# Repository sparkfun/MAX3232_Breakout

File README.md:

SparkFun Transceiver Breakout - MAX3232
===============================

[*SparkFun Transceiver Breakout - MAX3232 (BOB-11189)*](https://www.sparkfun.com/products/11189)

This is the RS232 converter IC that is capable of running at 3V and communicating with 5V logic.
We’ve taken the SOIC package MAX3232 and broken out all the pins you need to set up your RS232 to TTL connection. 
We’ve also included the necessary 0.1uF charge pump capacitors. 

Repository Contents
-------------------
* **/Hardware** - Eagle design files (.brd, .sch)
* **/Production** - Production panel files (.brd)

Documentation
-------------------
* **[Serial Communication](https://learn.sparkfun.com/tutorials/serial-communication)** - Basic tutorial on serial communication implemented on logic-level (TTL) and RS-232.
* **[Example Hookup Diagram](https://github.com/SparkfunTechSupport/Hookup-diagrams/blob/master/BOB-11189/BOB-11189%20hookup.jpg)**
* **[Fritzing Part](https://github.com/sparkfun/Fritzing_Parts/blob/main/products/11189-sfe_transceiver_breakout_max3232_rs232_converter_ttl.fzpz)**

License Information
-------------------

This product is _**open source**_! 

Please review the LICENSE.md file for license information. 

If you have any questions or concerns on licensing, please contact techsupport@sparkfun.com.

Distributed as-is; no warranty is given.

- Your friends at SparkFun.

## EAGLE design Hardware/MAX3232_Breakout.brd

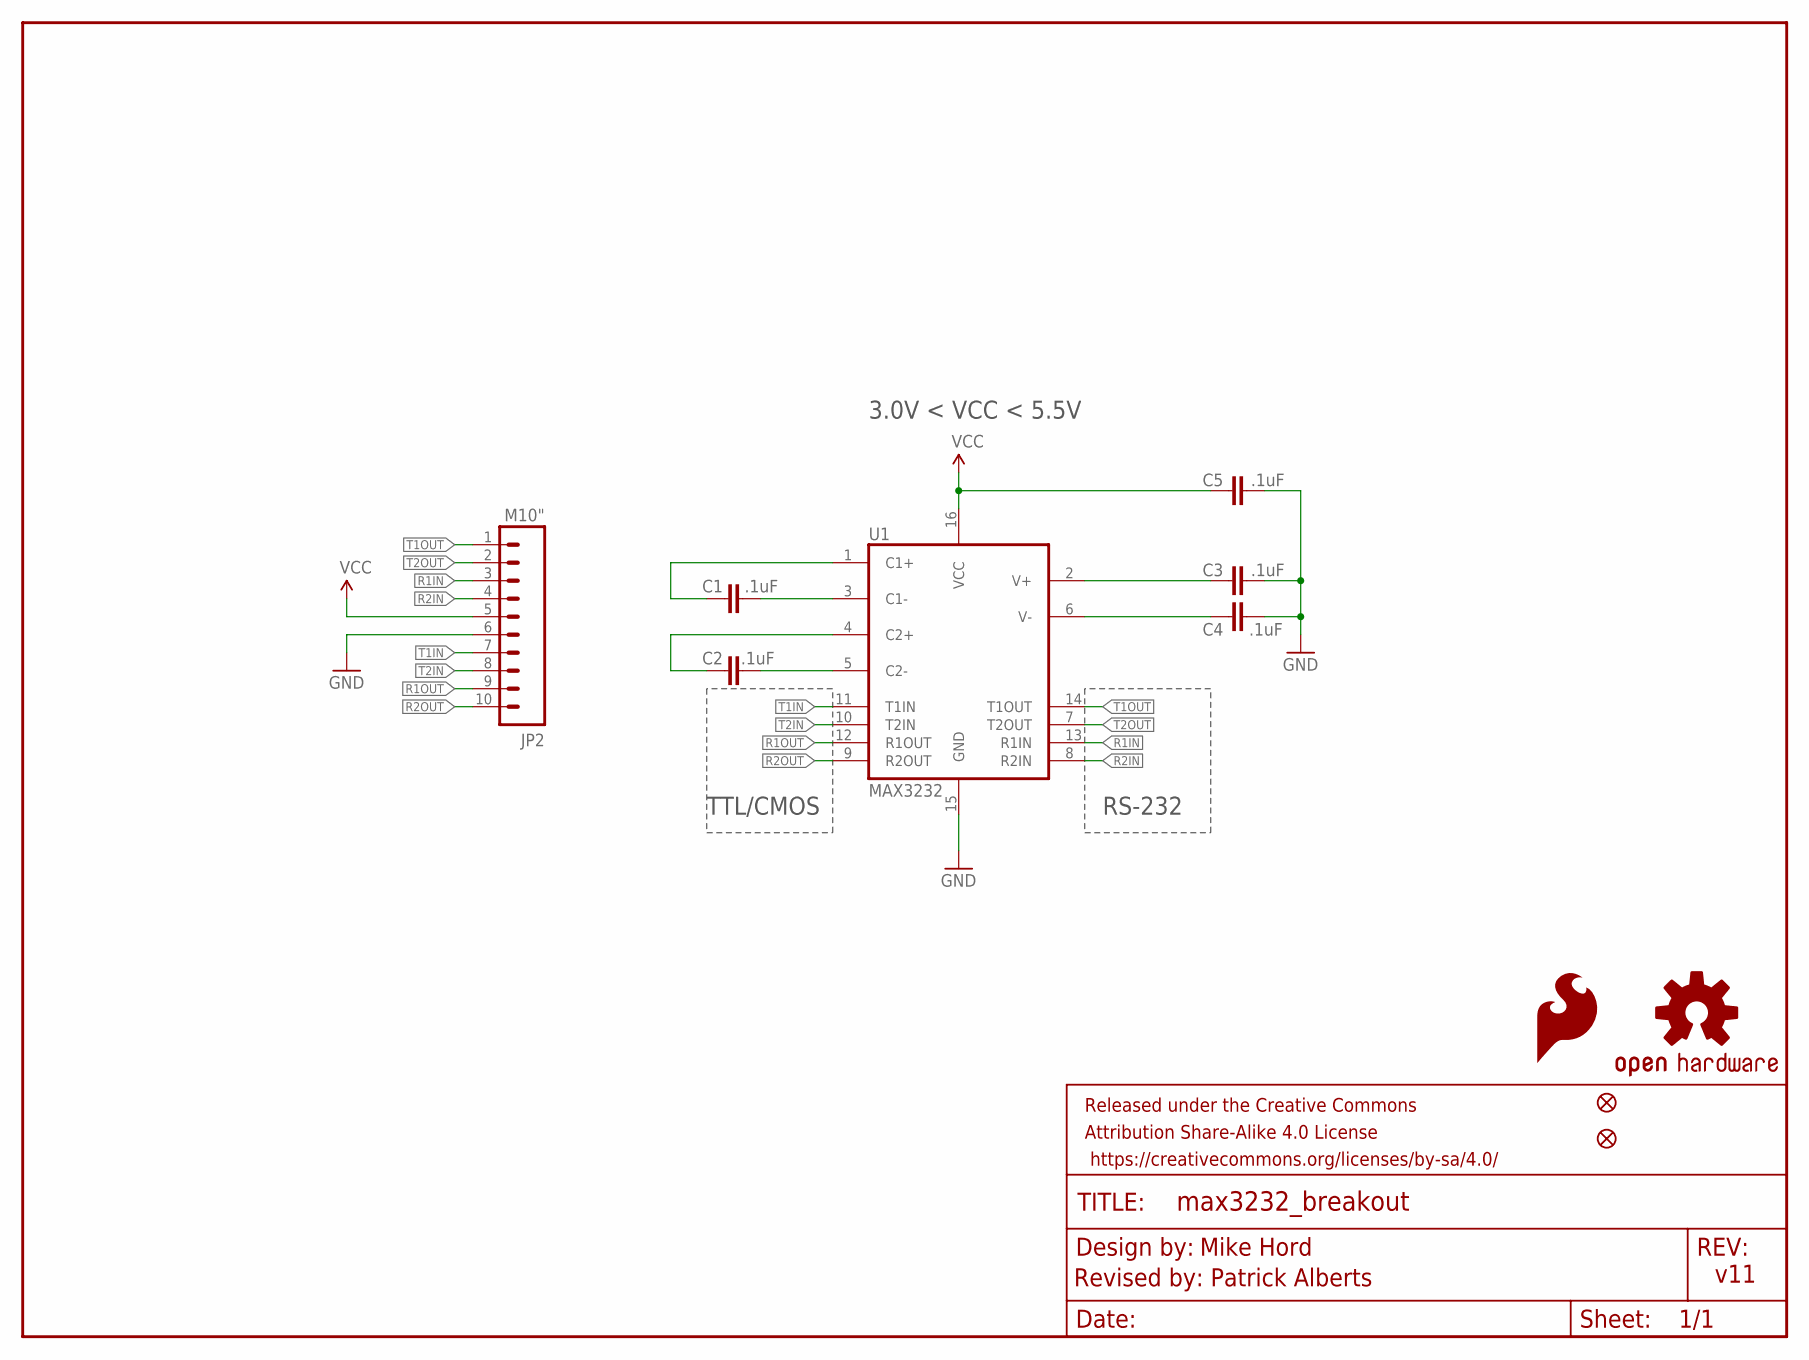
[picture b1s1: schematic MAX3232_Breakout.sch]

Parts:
C1, C2, C3, C4, C5: .1uF; 0603-CAP
FRAME1: FRAME-LETTER; CREATIVE_COMMONS
JP2: M10"; 1X10
JP3, JP4: FIDUCIALUFIDUCIAL; MICRO-FIDUCIAL
LOGO1: SFE_LOGO_FLAME.1_INCH; SFE_LOGO_FLAME_.1
U1: MAX3232; SO016
U$1: OSHW-LOGOS; OSHW-LOGO-S

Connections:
C1+: C1.1, U1.1 (C1+)
C1-: C1.2, U1.3 (C1-)
C2+: C2.1, U1.4 (C2+)
C2-: C2.2, U1.5 (C2-)
GND: C3.2, C4.2, C5.2, JP2.6, U1.15 (GND)
R1IN: JP2.3, U1.13 (R1IN)
R1OUT: JP2.9, U1.12 (R1OUT)
R2IN: JP2.4, U1.8 (R2IN)
R2OUT: JP2.10, U1.9 (R2OUT)
T1IN: JP2.7, U1.11 (T1IN)
T1OUT: JP2.1, U1.14 (T1OUT)
T2IN: JP2.8, U1.10 (T2IN)
T2OUT: JP2.2, U1.7 (T2OUT)
V+: C3.1, U1.2 (V+)
V-: C4.1, U1.6 (V-)
VCC: C5.1, JP2.5, U1.16 (VCC)

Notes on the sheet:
RS-232
TTL/CMOS
3.0V < VCC < 5.5V
Mike Hord
Revised by: Patrick Alberts
v11

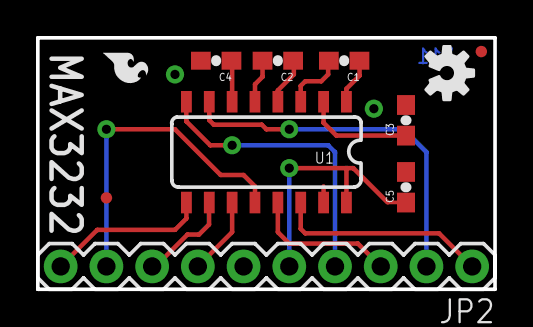
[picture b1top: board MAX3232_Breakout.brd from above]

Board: 2 copper layers, 25.4 x 14.0 mm, 12 parts (0 on the bottom side), 16 nets.

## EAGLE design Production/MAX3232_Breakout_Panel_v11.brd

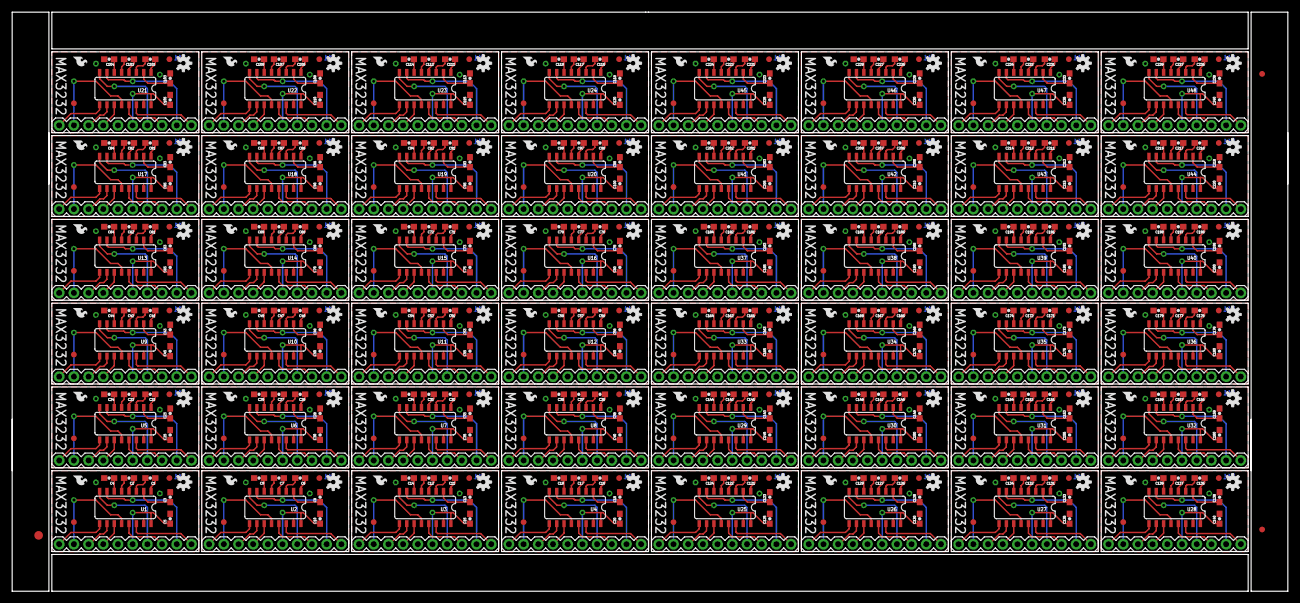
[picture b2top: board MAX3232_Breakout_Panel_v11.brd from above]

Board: 2 copper layers, 220.5 x 100.1 mm, 531 parts (0 on the bottom side), 768 nets.

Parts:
C1, C2, C3, C4, C5, C6, C7, C8, C9, C10, C11, C12, C13, C14, C15, C16, C17, C18, C19, C20, C21, C22, C23, C24, C25, C26, C27, C28, C29, C30, C31, C32, C33, C34, C35, C36, C37, C38, C39, C40, C41, C42, C43, C44, C45, C46, C47, C48, C49, C50, C51, C52, C53, C54, C55, C56, C57, C58, C59, C60, C61, C62, C63, C64, C65, C66, C67, C68, C69, C70, C71, C72, C73, C74, C75, C76, C77, C78, C79, C80, C81, C82, C83, C84, C85, C86, C87, C88, C89, C90, C91, C92, C93, C94, C95, C96, C97, C98, C99, C100, C101, C102, C103, C104, C105, C106, C107, C108, C109, C110, C111, C112, C113, C114, C115, C116, C117, C118, C119, C120, C121, C122, C123, C124, C125, C126, C127, C128, C129, C130, C131, C132, C133, C134, C135, C136, C137, C138, C139, C140, C141, C142, C143, C144, C145, C146, C147, C148, C149, C150, C151, C152, C153, C154, C155, C156, C157, C158, C159, C160, C161, C162, C163, C164, C165, C166, C167, C168, C169, C170, C171, C172, C173, C174, C175, C176, C177, C178, C179, C180, C181, C182, C183, C184, C185, C186, C187, C188, C189, C190, C191, C192, C193, C194, C195, C196, C197, C198, C199, C200, C201, C202, C203, C204, C205, C206, C207, C208, C209, C210, C211, C212, C213, C214, C215, C216, C217, C218, C219, C220, C221, C222, C223, C224, C225, C226, C227, C228, C229, C230, C231, C232, C233, C234, C235, C236, C237, C238, C239, C240: .1uF; 0603-CAP
E$1: FIDUCIAL-1.5X3
E$4, E$5: FIDUCIAL-1X2
FID1, FID2, FID3, FID4, FID5, FID6, FID7, FID8, FID9, FID10, FID11, FID12, FID13, FID14, FID15, FID16, FID17, FID18, FID19, FID20, FID21, FID22, FID23, FID24, FID25, FID26, FID27, FID28, FID29, FID30, FID31, FID32, FID33, FID34, FID35, FID36, FID37, FID38, FID39, FID40, FID41, FID42, FID43, FID44, FID45, FID46, FID47, FID48, FID49, FID50, FID51, FID52, FID53, FID54, FID55, FID56, FID57, FID58, FID59, FID60, FID61, FID62, FID63, FID64, FID65, FID66, FID67, FID68, FID69, FID70, FID71, FID72, FID73, FID74, FID75, FID76, FID77, FID78, FID79, FID80, FID81, FID82, FID83, FID84, FID85, FID86, FID87, FID88, FID89, FID90, FID91, FID92, FID93, FID94, FID95, FID96: FIDUCIAL1X2; FIDUCIAL-1X2
JP1, JP2, JP3, JP4, JP5, JP6, JP7, JP8, JP9, JP10, JP11, JP12, JP13, JP14, JP15, JP16, JP17, JP18, JP19, JP20, JP21, JP22, JP23, JP24, JP25, JP26, JP27, JP28, JP29, JP30, JP31, JP32, JP33, JP34, JP35, JP36, JP37, JP38, JP39, JP40, JP41, JP42, JP43, JP44, JP45, JP46, JP47, JP48: M10"; 1X10
LOGO1, LOGO2, LOGO3, LOGO4, LOGO5, LOGO6, LOGO7, LOGO8, LOGO9, LOGO10, LOGO11, LOGO12, LOGO13, LOGO14, LOGO15, LOGO16, LOGO17, LOGO18, LOGO19, LOGO20, LOGO21, LOGO22, LOGO23, LOGO24, LOGO25, LOGO26, LOGO27, LOGO28, LOGO29, LOGO30, LOGO31, LOGO32, LOGO33, LOGO34, LOGO35, LOGO36, LOGO37, LOGO38, LOGO39, LOGO40, LOGO41, LOGO42, LOGO43, LOGO44, LOGO45, LOGO46, LOGO47, LOGO48: SFE_LOGO_FLAME.1_INCH; SFE_LOGO_FLAME_.1
U1, U2, U3, U4, U5, U6, U7, U8, U9, U10, U11, U12, U13, U14, U15, U16, U17, U18, U19, U20, U21, U22, U23, U24, U25, U26, U27, U28, U29, U30, U31, U32, U33, U34, U35, U36, U37, U38, U39, U40, U41, U42, U43, U44, U45, U46, U47, U48: MAX3232; SO016
U$1, U$2, U$3, U$4, U$5, U$6, U$7, U$8, U$9, U$10, U$11, U$12, U$13, U$14, U$15, U$16, U$17, U$18, U$19, U$20, U$21, U$22, U$23, U$24, U$25, U$26, U$27, U$28, U$29, U$30, U$31, U$32, U$33, U$34, U$35, U$36, U$37, U$38, U$39, U$40, U$41, U$42, U$43, U$44, U$45, U$46, U$47, U$48: OSHW-LOGOS; OSHW-LOGO-S

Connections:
C1+: C1.1, U1.1
C1+1: C6.1, U2.1
C1+2: C11.1, U3.1
C1+3: C16.1, U4.1
C1+4: C21.1, U5.1
C1+5: C26.1, U6.1
C1+6: C31.1, U7.1
C1+7: C36.1, U8.1
C1+8: C41.1, U9.1
C1+9: C46.1, U10.1
C1+10: C51.1, U11.1
C1+11: C56.1, U12.1
C1+12: C61.1, U13.1
C1+13: C66.1, U14.1
C1+14: C71.1, U15.1
C1+15: C76.1, U16.1
C1+16: C81.1, U17.1
C1+17: C86.1, U18.1
C1+18: C91.1, U19.1
C1+19: C96.1, U20.1
C1+20: C101.1, U21.1
C1+21: C106.1, U22.1
C1+22: C111.1, U23.1
C1+23: C116.1, U24.1
C1+24: C121.1, U25.1
C1+25: C126.1, U26.1
C1+26: C131.1, U27.1
C1+27: C136.1, U28.1
C1+28: C141.1, U29.1
C1+29: C146.1, U30.1
C1+30: C151.1, U31.1
C1+31: C156.1, U32.1
C1+32: C161.1, U33.1
C1+33: C166.1, U34.1
C1+34: C171.1, U35.1
C1+35: C176.1, U36.1
C1+36: C181.1, U37.1
C1+37: C186.1, U38.1
C1+38: C191.1, U39.1
C1+39: C196.1, U40.1
C1+40: C201.1, U41.1
C1+41: C206.1, U42.1
C1+42: C211.1, U43.1
C1+43: C216.1, U44.1
C1+44: C221.1, U45.1
C1+45: C226.1, U46.1
C1+46: C231.1, U47.1
C1+47: C236.1, U48.1
C1-: C1.2, U1.3
C1-1: C6.2, U2.3
C1-2: C11.2, U3.3
C1-3: C16.2, U4.3
C1-4: C21.2, U5.3
C1-5: C26.2, U6.3
C1-6: C31.2, U7.3
C1-7: C36.2, U8.3
C1-8: C41.2, U9.3
C1-9: C46.2, U10.3
C1-10: C51.2, U11.3
C1-11: C56.2, U12.3
C1-12: C61.2, U13.3
C1-13: C66.2, U14.3
C1-14: C71.2, U15.3
C1-15: C76.2, U16.3
C1-16: C81.2, U17.3
C1-17: C86.2, U18.3
C1-18: C91.2, U19.3
C1-19: C96.2, U20.3
C1-20: C101.2, U21.3
C1-21: C106.2, U22.3
C1-22: C111.2, U23.3
C1-23: C116.2, U24.3
C1-24: C121.2, U25.3
C1-25: C126.2, U26.3
C1-26: C131.2, U27.3
C1-27: C136.2, U28.3
C1-28: C141.2, U29.3
C1-29: C146.2, U30.3
C1-30: C151.2, U31.3
C1-31: C156.2, U32.3
C1-32: C161.2, U33.3
C1-33: C166.2, U34.3
C1-34: C171.2, U35.3
C1-35: C176.2, U36.3
C1-36: C181.2, U37.3
C1-37: C186.2, U38.3
C1-38: C191.2, U39.3
C1-39: C196.2, U40.3
C1-40: C201.2, U41.3
C1-41: C206.2, U42.3
C1-42: C211.2, U43.3
C1-43: C216.2, U44.3
C1-44: C221.2, U45.3
C1-45: C226.2, U46.3
C1-46: C231.2, U47.3
C1-47: C236.2, U48.3
C2+: C2.1, U1.4
C2+1: C7.1, U2.4
C2+2: C12.1, U3.4
C2+3: C17.1, U4.4
C2+4: C22.1, U5.4
C2+5: C27.1, U6.4
C2+6: C32.1, U7.4
C2+7: C37.1, U8.4
C2+8: C42.1, U9.4
C2+9: C47.1, U10.4
C2+10: C52.1, U11.4
C2+11: C57.1, U12.4
C2+12: C62.1, U13.4
C2+13: C67.1, U14.4
C2+14: C72.1, U15.4
C2+15: C77.1, U16.4
C2+16: C82.1, U17.4
C2+17: C87.1, U18.4
C2+18: C92.1, U19.4
C2+19: C97.1, U20.4
C2+20: C102.1, U21.4
C2+21: C107.1, U22.4
C2+22: C112.1, U23.4
C2+23: C117.1, U24.4
C2+24: C122.1, U25.4
C2+25: C127.1, U26.4
C2+26: C132.1, U27.4
C2+27: C137.1, U28.4
C2+28: C142.1, U29.4
C2+29: C147.1, U30.4
C2+30: C152.1, U31.4
C2+31: C157.1, U32.4
C2+32: C162.1, U33.4
C2+33: C167.1, U34.4
C2+34: C172.1, U35.4
C2+35: C177.1, U36.4
C2+36: C182.1, U37.4
C2+37: C187.1, U38.4
C2+38: C192.1, U39.4
C2+39: C197.1, U40.4
C2+40: C202.1, U41.4
C2+41: C207.1, U42.4
C2+42: C212.1, U43.4
C2+43: C217.1, U44.4
C2+44: C222.1, U45.4
C2+45: C227.1, U46.4
C2+46: C232.1, U47.4
C2+47: C237.1, U48.4
C2-: C2.2, U1.5
C2-1: C7.2, U2.5
C2-2: C12.2, U3.5
C2-3: C17.2, U4.5
C2-4: C22.2, U5.5
C2-5: C27.2, U6.5
C2-6: C32.2, U7.5
C2-7: C37.2, U8.5
C2-8: C42.2, U9.5
C2-9: C47.2, U10.5
C2-10: C52.2, U11.5
C2-11: C57.2, U12.5
C2-12: C62.2, U13.5
C2-13: C67.2, U14.5
C2-14: C72.2, U15.5
C2-15: C77.2, U16.5
C2-16: C82.2, U17.5
C2-17: C87.2, U18.5
C2-18: C92.2, U19.5
C2-19: C97.2, U20.5
C2-20: C102.2, U21.5
C2-21: C107.2, U22.5
C2-22: C112.2, U23.5
C2-23: C117.2, U24.5
C2-24: C122.2, U25.5
C2-25: C127.2, U26.5
C2-26: C132.2, U27.5
C2-27: C137.2, U28.5
C2-28: C142.2, U29.5
C2-29: C147.2, U30.5
C2-30: C152.2, U31.5
C2-31: C157.2, U32.5
C2-32: C162.2, U33.5
C2-33: C167.2, U34.5
C2-34: C172.2, U35.5
C2-35: C177.2, U36.5
C2-36: C182.2, U37.5
C2-37: C187.2, U38.5
C2-38: C192.2, U39.5
C2-39: C197.2, U40.5
C2-40: C202.2, U41.5
C2-41: C207.2, U42.5
C2-42: C212.2, U43.5
C2-43: C217.2, U44.5
C2-44: C222.2, U45.5
C2-45: C227.2, U46.5
C2-46: C232.2, U47.5
C2-47: C237.2, U48.5
GND: C3.2, C4.2, C5.2, JP2.6, U1.15
GND1: C8.2, C9.2, C10.2, JP1.6, U2.15
GND2: C13.2, C14.2, C15.2, JP3.6, U3.15
GND3: C18.2, C19.2, C20.2, JP4.6, U4.15
GND4: C23.2, C24.2, C25.2, JP5.6, U5.15
GND5: C28.2, C29.2, C30.2, JP6.6, U6.15
GND6: C33.2, C34.2, C35.2, JP7.6, U7.15
GND7: C38.2, C39.2, C40.2, JP8.6, U8.15
GND8: C43.2, C44.2, C45.2, JP9.6, U9.15
GND9: C48.2, C49.2, C50.2, JP10.6, U10.15
GND10: C53.2, C54.2, C55.2, JP11.6, U11.15
GND11: C58.2, C59.2, C60.2, JP12.6, U12.15
GND12: C63.2, C64.2, C65.2, JP13.6, U13.15
GND13: C68.2, C69.2, C70.2, JP14.6, U14.15
GND14: C73.2, C74.2, C75.2, JP15.6, U15.15
GND15: C78.2, C79.2, C80.2, JP16.6, U16.15
GND16: C83.2, C84.2, C85.2, JP17.6, U17.15
GND17: C88.2, C89.2, C90.2, JP18.6, U18.15
GND18: C93.2, C94.2, C95.2, JP19.6, U19.15
GND19: C98.2, C99.2, C100.2, JP20.6, U20.15
GND20: C103.2, C104.2, C105.2, JP21.6, U21.15
GND21: C108.2, C109.2, C110.2, JP22.6, U22.15
GND22: C113.2, C114.2, C115.2, JP23.6, U23.15
GND23: C118.2, C119.2, C120.2, JP24.6, U24.15
GND24: C123.2, C124.2, C125.2, JP25.6, U25.15
GND25: C128.2, C129.2, C130.2, JP26.6, U26.15
GND26: C133.2, C134.2, C135.2, JP27.6, U27.15
GND27: C138.2, C139.2, C140.2, JP28.6, U28.15
GND28: C143.2, C144.2, C145.2, JP29.6, U29.15
GND29: C148.2, C149.2, C150.2, JP30.6, U30.15
GND30: C153.2, C154.2, C155.2, JP31.6, U31.15
GND31: C158.2, C159.2, C160.2, JP32.6, U32.15
GND32: C163.2, C164.2, C165.2, JP33.6, U33.15
GND33: C168.2, C169.2, C170.2, JP34.6, U34.15
GND34: C173.2, C174.2, C175.2, JP35.6, U35.15
GND35: C178.2, C179.2, C180.2, JP36.6, U36.15
GND36: C183.2, C184.2, C185.2, JP37.6, U37.15
GND37: C188.2, C189.2, C190.2, JP38.6, U38.15
GND38: C193.2, C194.2, C195.2, JP39.6, U39.15
GND39: C198.2, C199.2, C200.2, JP40.6, U40.15
GND40: C203.2, C204.2, C205.2, JP41.6, U41.15
GND41: C208.2, C209.2, C210.2, JP42.6, U42.15
GND42: C213.2, C214.2, C215.2, JP43.6, U43.15
GND43: C218.2, C219.2, C220.2, JP44.6, U44.15
GND44: C223.2, C224.2, C225.2, JP45.6, U45.15
GND45: C228.2, C229.2, C230.2, JP46.6, U46.15
GND46: C233.2, C234.2, C235.2, JP47.6, U47.15
GND47: C238.2, C239.2, C240.2, JP48.6, U48.15
R1IN: JP2.3, U1.13
R1IN1: JP1.3, U2.13
R1IN2: JP3.3, U3.13
R1IN3: JP4.3, U4.13
R1IN4: JP5.3, U5.13
R1IN5: JP6.3, U6.13
R1IN6: JP7.3, U7.13
R1IN7: JP8.3, U8.13
R1IN8: JP9.3, U9.13
R1IN9: JP10.3, U10.13
R1IN10: JP11.3, U11.13
R1IN11: JP12.3, U12.13
R1IN12: JP13.3, U13.13
R1IN13: JP14.3, U14.13
R1IN14: JP15.3, U15.13
R1IN15: JP16.3, U16.13
R1IN16: JP17.3, U17.13
R1IN17: JP18.3, U18.13
R1IN18: JP19.3, U19.13
R1IN19: JP20.3, U20.13
R1IN20: JP21.3, U21.13
R1IN21: JP22.3, U22.13
R1IN22: JP23.3, U23.13
R1IN23: JP24.3, U24.13
R1IN24: JP25.3, U25.13
R1IN25: JP26.3, U26.13
R1IN26: JP27.3, U27.13
R1IN27: JP28.3, U28.13
R1IN28: JP29.3, U29.13
R1IN29: JP30.3, U30.13
R1IN30: JP31.3, U31.13
R1IN31: JP32.3, U32.13
R1IN32: JP33.3, U33.13
R1IN33: JP34.3, U34.13
R1IN34: JP35.3, U35.13
R1IN35: JP36.3, U36.13
R1IN36: JP37.3, U37.13
R1IN37: JP38.3, U38.13
R1IN38: JP39.3, U39.13
R1IN39: JP40.3, U40.13
R1IN40: JP41.3, U41.13
R1IN41: JP42.3, U42.13
R1IN42: JP43.3, U43.13
R1IN43: JP44.3, U44.13
R1IN44: JP45.3, U45.13
R1IN45: JP46.3, U46.13
R1IN46: JP47.3, U47.13
R1IN47: JP48.3, U48.13
R1OUT: JP2.9, U1.12
R1OUT1: JP1.9, U2.12
R1OUT2: JP3.9, U3.12
R1OUT3: JP4.9, U4.12
R1OUT4: JP5.9, U5.12
R1OUT5: JP6.9, U6.12
R1OUT6: JP7.9, U7.12
R1OUT7: JP8.9, U8.12
R1OUT8: JP9.9, U9.12
R1OUT9: JP10.9, U10.12
R1OUT10: JP11.9, U11.12
R1OUT11: JP12.9, U12.12
R1OUT12: JP13.9, U13.12
R1OUT13: JP14.9, U14.12
R1OUT14: JP15.9, U15.12
R1OUT15: JP16.9, U16.12
R1OUT16: JP17.9, U17.12
R1OUT17: JP18.9, U18.12
R1OUT18: JP19.9, U19.12
R1OUT19: JP20.9, U20.12
R1OUT20: JP21.9, U21.12
R1OUT21: JP22.9, U22.12
R1OUT22: JP23.9, U23.12
R1OUT23: JP24.9, U24.12
R1OUT24: JP25.9, U25.12
R1OUT25: JP26.9, U26.12
R1OUT26: JP27.9, U27.12
R1OUT27: JP28.9, U28.12
R1OUT28: JP29.9, U29.12
R1OUT29: JP30.9, U30.12
R1OUT30: JP31.9, U31.12
R1OUT31: JP32.9, U32.12
R1OUT32: JP33.9, U33.12
R1OUT33: JP34.9, U34.12
R1OUT34: JP35.9, U35.12
R1OUT35: JP36.9, U36.12
R1OUT36: JP37.9, U37.12
R1OUT37: JP38.9, U38.12
R1OUT38: JP39.9, U39.12
R1OUT39: JP40.9, U40.12
R1OUT40: JP41.9, U41.12
R1OUT41: JP42.9, U42.12
R1OUT42: JP43.9, U43.12
R1OUT43: JP44.9, U44.12
R1OUT44: JP45.9, U45.12
R1OUT45: JP46.9, U46.12
R1OUT46: JP47.9, U47.12
R1OUT47: JP48.9, U48.12
R2IN: JP2.4, U1.8
R2IN1: JP1.4, U2.8
R2IN2: JP3.4, U3.8
R2IN3: JP4.4, U4.8
R2IN4: JP5.4, U5.8
R2IN5: JP6.4, U6.8
R2IN6: JP7.4, U7.8
R2IN7: JP8.4, U8.8
R2IN8: JP9.4, U9.8
R2IN9: JP10.4, U10.8
R2IN10: JP11.4, U11.8
R2IN11: JP12.4, U12.8
R2IN12: JP13.4, U13.8
R2IN13: JP14.4, U14.8
R2IN14: JP15.4, U15.8
R2IN15: JP16.4, U16.8
R2IN16: JP17.4, U17.8
R2IN17: JP18.4, U18.8
R2IN18: JP19.4, U19.8
R2IN19: JP20.4, U20.8
R2IN20: JP21.4, U21.8
R2IN21: JP22.4, U22.8
R2IN22: JP23.4, U23.8
R2IN23: JP24.4, U24.8
R2IN24: JP25.4, U25.8
R2IN25: JP26.4, U26.8
R2IN26: JP27.4, U27.8
R2IN27: JP28.4, U28.8
R2IN28: JP29.4, U29.8
R2IN29: JP30.4, U30.8
R2IN30: JP31.4, U31.8
R2IN31: JP32.4, U32.8
R2IN32: JP33.4, U33.8
R2IN33: JP34.4, U34.8
R2IN34: JP35.4, U35.8
R2IN35: JP36.4, U36.8
R2IN36: JP37.4, U37.8
R2IN37: JP38.4, U38.8
R2IN38: JP39.4, U39.8
R2IN39: JP40.4, U40.8
R2IN40: JP41.4, U41.8
R2IN41: JP42.4, U42.8
R2IN42: JP43.4, U43.8
R2IN43: JP44.4, U44.8
R2IN44: JP45.4, U45.8
R2IN45: JP46.4, U46.8
R2IN46: JP47.4, U47.8
R2IN47: JP48.4, U48.8
R2OUT: JP2.10, U1.9
R2OUT1: JP1.10, U2.9
R2OUT2: JP3.10, U3.9
R2OUT3: JP4.10, U4.9
R2OUT4: JP5.10, U5.9
R2OUT5: JP6.10, U6.9
R2OUT6: JP7.10, U7.9
R2OUT7: JP8.10, U8.9
R2OUT8: JP9.10, U9.9
R2OUT9: JP10.10, U10.9
R2OUT10: JP11.10, U11.9
R2OUT11: JP12.10, U12.9
R2OUT12: JP13.10, U13.9
R2OUT13: JP14.10, U14.9
R2OUT14: JP15.10, U15.9
R2OUT15: JP16.10, U16.9
R2OUT16: JP17.10, U17.9
R2OUT17: JP18.10, U18.9
R2OUT18: JP19.10, U19.9
R2OUT19: JP20.10, U20.9
R2OUT20: JP21.10, U21.9
R2OUT21: JP22.10, U22.9
R2OUT22: JP23.10, U23.9
R2OUT23: JP24.10, U24.9
R2OUT24: JP25.10, U25.9
R2OUT25: JP26.10, U26.9
R2OUT26: JP27.10, U27.9
R2OUT27: JP28.10, U28.9
R2OUT28: JP29.10, U29.9
R2OUT29: JP30.10, U30.9
R2OUT30: JP31.10, U31.9
R2OUT31: JP32.10, U32.9
R2OUT32: JP33.10, U33.9
R2OUT33: JP34.10, U34.9
R2OUT34: JP35.10, U35.9
R2OUT35: JP36.10, U36.9
R2OUT36: JP37.10, U37.9
R2OUT37: JP38.10, U38.9
R2OUT38: JP39.10, U39.9
R2OUT39: JP40.10, U40.9
R2OUT40: JP41.10, U41.9
R2OUT41: JP42.10, U42.9
R2OUT42: JP43.10, U43.9
R2OUT43: JP44.10, U44.9
R2OUT44: JP45.10, U45.9
R2OUT45: JP46.10, U46.9
R2OUT46: JP47.10, U47.9
R2OUT47: JP48.10, U48.9
T1IN: JP2.7, U1.11
T1IN1: JP1.7, U2.11
T1IN2: JP3.7, U3.11
T1IN3: JP4.7, U4.11
T1IN4: JP5.7, U5.11
T1IN5: JP6.7, U6.11
T1IN6: JP7.7, U7.11
T1IN7: JP8.7, U8.11
T1IN8: JP9.7, U9.11
T1IN9: JP10.7, U10.11
T1IN10: JP11.7, U11.11
T1IN11: JP12.7, U12.11
T1IN12: JP13.7, U13.11
T1IN13: JP14.7, U14.11
T1IN14: JP15.7, U15.11
T1IN15: JP16.7, U16.11
T1IN16: JP17.7, U17.11
T1IN17: JP18.7, U18.11
T1IN18: JP19.7, U19.11
T1IN19: JP20.7, U20.11
T1IN20: JP21.7, U21.11
T1IN21: JP22.7, U22.11
T1IN22: JP23.7, U23.11
T1IN23: JP24.7, U24.11
T1IN24: JP25.7, U25.11
T1IN25: JP26.7, U26.11
T1IN26: JP27.7, U27.11
T1IN27: JP28.7, U28.11
T1IN28: JP29.7, U29.11
T1IN29: JP30.7, U30.11
T1IN30: JP31.7, U31.11
T1IN31: JP32.7, U32.11
T1IN32: JP33.7, U33.11
T1IN33: JP34.7, U34.11
T1IN34: JP35.7, U35.11
T1IN35: JP36.7, U36.11
T1IN36: JP37.7, U37.11
T1IN37: JP38.7, U38.11
T1IN38: JP39.7, U39.11
T1IN39: JP40.7, U40.11
T1IN40: JP41.7, U41.11
T1IN41: JP42.7, U42.11
T1IN42: JP43.7, U43.11
T1IN43: JP44.7, U44.11
T1IN44: JP45.7, U45.11
T1IN45: JP46.7, U46.11
T1IN46: JP47.7, U47.11
T1IN47: JP48.7, U48.11
T1OUT: JP2.1, U1.14
T1OUT1: JP1.1, U2.14
T1OUT2: JP3.1, U3.14
T1OUT3: JP4.1, U4.14
T1OUT4: JP5.1, U5.14
T1OUT5: JP6.1, U6.14
T1OUT6: JP7.1, U7.14
T1OUT7: JP8.1, U8.14
T1OUT8: JP9.1, U9.14
T1OUT9: JP10.1, U10.14
T1OUT10: JP11.1, U11.14
T1OUT11: JP12.1, U12.14
T1OUT12: JP13.1, U13.14
T1OUT13: JP14.1, U14.14
T1OUT14: JP15.1, U15.14
T1OUT15: JP16.1, U16.14
T1OUT16: JP17.1, U17.14
T1OUT17: JP18.1, U18.14
T1OUT18: JP19.1, U19.14
T1OUT19: JP20.1, U20.14
T1OUT20: JP21.1, U21.14
T1OUT21: JP22.1, U22.14
T1OUT22: JP23.1, U23.14
T1OUT23: JP24.1, U24.14
T1OUT24: JP25.1, U25.14
T1OUT25: JP26.1, U26.14
T1OUT26: JP27.1, U27.14
T1OUT27: JP28.1, U28.14
T1OUT28: JP29.1, U29.14
T1OUT29: JP30.1, U30.14
T1OUT30: JP31.1, U31.14
T1OUT31: JP32.1, U32.14
T1OUT32: JP33.1, U33.14
T1OUT33: JP34.1, U34.14
T1OUT34: JP35.1, U35.14
T1OUT35: JP36.1, U36.14
T1OUT36: JP37.1, U37.14
T1OUT37: JP38.1, U38.14
T1OUT38: JP39.1, U39.14
T1OUT39: JP40.1, U40.14
T1OUT40: JP41.1, U41.14
T1OUT41: JP42.1, U42.14
T1OUT42: JP43.1, U43.14
T1OUT43: JP44.1, U44.14
T1OUT44: JP45.1, U45.14
T1OUT45: JP46.1, U46.14
T1OUT46: JP47.1, U47.14
T1OUT47: JP48.1, U48.14
T2IN: JP2.8, U1.10
T2IN1: JP1.8, U2.10
T2IN2: JP3.8, U3.10
T2IN3: JP4.8, U4.10
T2IN4: JP5.8, U5.10
T2IN5: JP6.8, U6.10
T2IN6: JP7.8, U7.10
T2IN7: JP8.8, U8.10
T2IN8: JP9.8, U9.10
T2IN9: JP10.8, U10.10
T2IN10: JP11.8, U11.10
T2IN11: JP12.8, U12.10
T2IN12: JP13.8, U13.10
T2IN13: JP14.8, U14.10
T2IN14: JP15.8, U15.10
T2IN15: JP16.8, U16.10
T2IN16: JP17.8, U17.10
T2IN17: JP18.8, U18.10
T2IN18: JP19.8, U19.10
T2IN19: JP20.8, U20.10
T2IN20: JP21.8, U21.10
T2IN21: JP22.8, U22.10
T2IN22: JP23.8, U23.10
T2IN23: JP24.8, U24.10
T2IN24: JP25.8, U25.10
T2IN25: JP26.8, U26.10
T2IN26: JP27.8, U27.10
T2IN27: JP28.8, U28.10
T2IN28: JP29.8, U29.10
T2IN29: JP30.8, U30.10
T2IN30: JP31.8, U31.10
T2IN31: JP32.8, U32.10
T2IN32: JP33.8, U33.10
T2IN33: JP34.8, U34.10
T2IN34: JP35.8, U35.10
T2IN35: JP36.8, U36.10
T2IN36: JP37.8, U37.10
T2IN37: JP38.8, U38.10
T2IN38: JP39.8, U39.10
T2IN39: JP40.8, U40.10
T2IN40: JP41.8, U41.10
T2IN41: JP42.8, U42.10
T2IN42: JP43.8, U43.10
T2IN43: JP44.8, U44.10
T2IN44: JP45.8, U45.10
T2IN45: JP46.8, U46.10
T2IN46: JP47.8, U47.10
T2IN47: JP48.8, U48.10
T2OUT: JP2.2, U1.7
T2OUT1: JP1.2, U2.7
T2OUT2: JP3.2, U3.7
T2OUT3: JP4.2, U4.7
T2OUT4: JP5.2, U5.7
T2OUT5: JP6.2, U6.7
T2OUT6: JP7.2, U7.7
T2OUT7: JP8.2, U8.7
T2OUT8: JP9.2, U9.7
T2OUT9: JP10.2, U10.7
T2OUT10: JP11.2, U11.7
T2OUT11: JP12.2, U12.7
T2OUT12: JP13.2, U13.7
T2OUT13: JP14.2, U14.7
T2OUT14: JP15.2, U15.7
T2OUT15: JP16.2, U16.7
T2OUT16: JP17.2, U17.7
T2OUT17: JP18.2, U18.7
T2OUT18: JP19.2, U19.7
T2OUT19: JP20.2, U20.7
T2OUT20: JP21.2, U21.7
T2OUT21: JP22.2, U22.7
T2OUT22: JP23.2, U23.7
T2OUT23: JP24.2, U24.7
T2OUT24: JP25.2, U25.7
T2OUT25: JP26.2, U26.7
T2OUT26: JP27.2, U27.7
T2OUT27: JP28.2, U28.7
T2OUT28: JP29.2, U29.7
T2OUT29: JP30.2, U30.7
T2OUT30: JP31.2, U31.7
T2OUT31: JP32.2, U32.7
T2OUT32: JP33.2, U33.7
T2OUT33: JP34.2, U34.7
T2OUT34: JP35.2, U35.7
T2OUT35: JP36.2, U36.7
T2OUT36: JP37.2, U37.7
T2OUT37: JP38.2, U38.7
T2OUT38: JP39.2, U39.7
T2OUT39: JP40.2, U40.7
T2OUT40: JP41.2, U41.7
T2OUT41: JP42.2, U42.7
T2OUT42: JP43.2, U43.7
T2OUT43: JP44.2, U44.7
T2OUT44: JP45.2, U45.7
T2OUT45: JP46.2, U46.7
T2OUT46: JP47.2, U47.7
T2OUT47: JP48.2, U48.7
V+: C3.1, U1.2
V+1: C8.1, U2.2
V+2: C13.1, U3.2
V+3: C18.1, U4.2
V+4: C23.1, U5.2
V+5: C28.1, U6.2
V+6: C33.1, U7.2
V+7: C38.1, U8.2
V+8: C43.1, U9.2
V+9: C48.1, U10.2
V+10: C53.1, U11.2
V+11: C58.1, U12.2
V+12: C63.1, U13.2
V+13: C68.1, U14.2
V+14: C73.1, U15.2
V+15: C78.1, U16.2
V+16: C83.1, U17.2
V+17: C88.1, U18.2
V+18: C93.1, U19.2
V+19: C98.1, U20.2
V+20: C103.1, U21.2
V+21: C108.1, U22.2
V+22: C113.1, U23.2
V+23: C118.1, U24.2
V+24: C123.1, U25.2
V+25: C128.1, U26.2
V+26: C133.1, U27.2
V+27: C138.1, U28.2
V+28: C143.1, U29.2
V+29: C148.1, U30.2
V+30: C153.1, U31.2
V+31: C158.1, U32.2
V+32: C163.1, U33.2
V+33: C168.1, U34.2
V+34: C173.1, U35.2
V+35: C178.1, U36.2
V+36: C183.1, U37.2
V+37: C188.1, U38.2
V+38: C193.1, U39.2
V+39: C198.1, U40.2
V+40: C203.1, U41.2
V+41: C208.1, U42.2
V+42: C213.1, U43.2
V+43: C218.1, U44.2
V+44: C223.1, U45.2
V+45: C228.1, U46.2
V+46: C233.1, U47.2
V+47: C238.1, U48.2
V-: C4.1, U1.6
V-1: C9.1, U2.6
V-2: C14.1, U3.6
V-3: C19.1, U4.6
V-4: C24.1, U5.6
V-5: C29.1, U6.6
V-6: C34.1, U7.6
V-7: C39.1, U8.6
V-8: C44.1, U9.6
V-9: C49.1, U10.6
V-10: C54.1, U11.6
V-11: C59.1, U12.6
V-12: C64.1, U13.6
V-13: C69.1, U14.6
V-14: C74.1, U15.6
V-15: C79.1, U16.6
V-16: C84.1, U17.6
V-17: C89.1, U18.6
V-18: C94.1, U19.6
V-19: C99.1, U20.6
V-20: C104.1, U21.6
V-21: C109.1, U22.6
V-22: C114.1, U23.6
V-23: C119.1, U24.6
V-24: C124.1, U25.6
V-25: C129.1, U26.6
V-26: C134.1, U27.6
V-27: C139.1, U28.6
V-28: C144.1, U29.6
V-29: C149.1, U30.6
V-30: C154.1, U31.6
V-31: C159.1, U32.6
V-32: C164.1, U33.6
V-33: C169.1, U34.6
V-34: C174.1, U35.6
V-35: C179.1, U36.6
V-36: C184.1, U37.6
V-37: C189.1, U38.6
V-38: C194.1, U39.6
V-39: C199.1, U40.6
V-40: C204.1, U41.6
V-41: C209.1, U42.6
V-42: C214.1, U43.6
V-43: C219.1, U44.6
V-44: C224.1, U45.6
V-45: C229.1, U46.6
V-46: C234.1, U47.6
V-47: C239.1, U48.6
VCC: C5.1, JP2.5, U1.16
VCC1: C10.1, JP1.5, U2.16
VCC2: C15.1, JP3.5, U3.16
VCC3: C20.1, JP4.5, U4.16
VCC4: C25.1, JP5.5, U5.16
VCC5: C30.1, JP6.5, U6.16
VCC6: C35.1, JP7.5, U7.16
VCC7: C40.1, JP8.5, U8.16
VCC8: C45.1, JP9.5, U9.16
VCC9: C50.1, JP10.5, U10.16
VCC10: C55.1, JP11.5, U11.16
VCC11: C60.1, JP12.5, U12.16
VCC12: C65.1, JP13.5, U13.16
VCC13: C70.1, JP14.5, U14.16
VCC14: C75.1, JP15.5, U15.16
VCC15: C80.1, JP16.5, U16.16
VCC16: C85.1, JP17.5, U17.16
VCC17: C90.1, JP18.5, U18.16
VCC18: C95.1, JP19.5, U19.16
VCC19: C100.1, JP20.5, U20.16
VCC20: C105.1, JP21.5, U21.16
VCC21: C110.1, JP22.5, U22.16
VCC22: C115.1, JP23.5, U23.16
VCC23: C120.1, JP24.5, U24.16
VCC24: C125.1, JP25.5, U25.16
VCC25: C130.1, JP26.5, U26.16
VCC26: C135.1, JP27.5, U27.16
VCC27: C140.1, JP28.5, U28.16
VCC28: C145.1, JP29.5, U29.16
VCC29: C150.1, JP30.5, U30.16
VCC30: C155.1, JP31.5, U31.16
VCC31: C160.1, JP32.5, U32.16
VCC32: C165.1, JP33.5, U33.16
VCC33: C170.1, JP34.5, U34.16
VCC34: C175.1, JP35.5, U35.16
VCC35: C180.1, JP36.5, U36.16
VCC36: C185.1, JP37.5, U37.16
VCC37: C190.1, JP38.5, U38.16
VCC38: C195.1, JP39.5, U39.16
VCC39: C200.1, JP40.5, U40.16
VCC40: C205.1, JP41.5, U41.16
VCC41: C210.1, JP42.5, U42.16
VCC42: C215.1, JP43.5, U43.16
VCC43: C220.1, JP44.5, U44.16
VCC44: C225.1, JP45.5, U45.16
VCC45: C230.1, JP46.5, U46.16
VCC46: C235.1, JP47.5, U47.16
VCC47: C240.1, JP48.5, U48.16

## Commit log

2014-12-22 Initial Commit.
2015-01-08 Updated to 0603, added attributes.
2015-01-08 Fixed SCH, re route trace and trestrict
2015-01-08 Fixed t res and schematic
2015-02-04 Fixed final qc checklist items.
2015-02-11 switched fids to regular size
2015-02-11 created panel v11
2015-07-06 Adding license &.git files, updating README
2015-07-06 Fixing product url links
2018-04-16 New panel

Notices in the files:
parts and their libraries:
SparkFun-Aesthetics: Licensing: CC v3.0 Share-Alike You are welcome to use this library for commercial purposes.
SparkFun-Aesthetics: Released under the Creative Commons Attribution Share-Alike 3.0 License
SparkFun-Aesthetics: http://creativecommons.org/licenses/by-sa/3.0
